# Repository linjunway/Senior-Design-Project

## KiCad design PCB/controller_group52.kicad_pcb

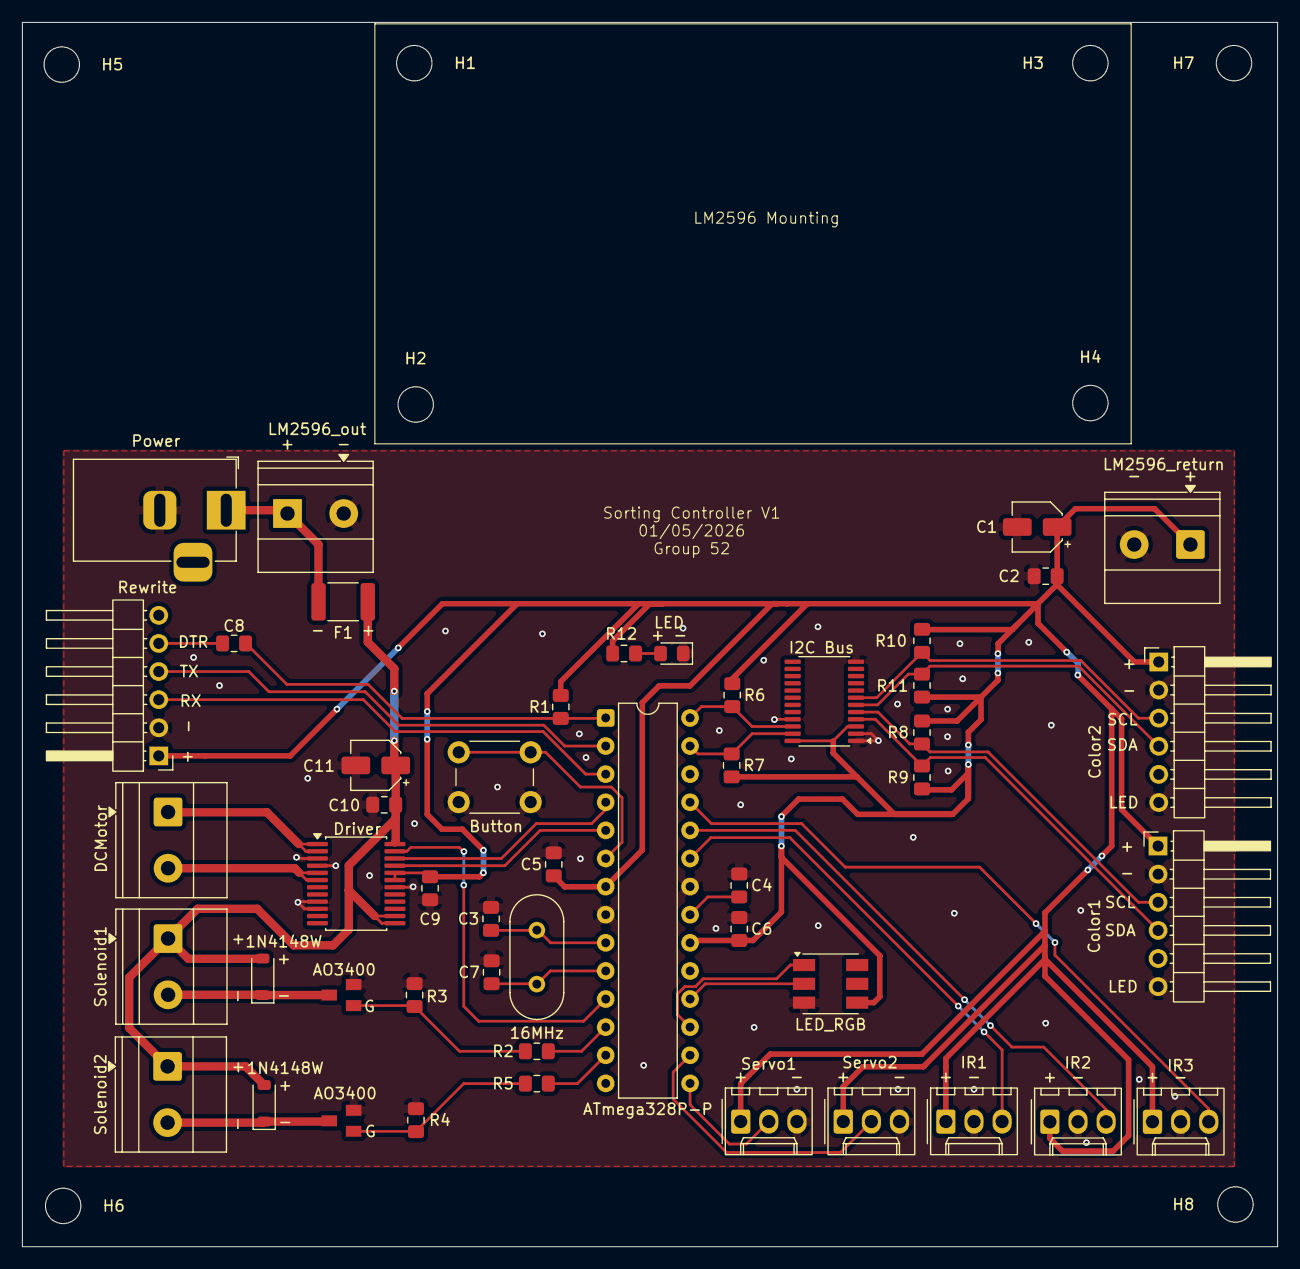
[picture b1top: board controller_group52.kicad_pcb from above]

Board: 2 copper layers, 113.4 x 110.6 mm, 57 parts (0 on the bottom side), 37 nets.

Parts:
C1, C11: 10uF; CP_Elec_4x5.4
C2: 1uF; C_0805_2012Metric_Pad1.18x1.45mm_HandSolder
C3, C7: 22pF; C_0805_2012Metric_Pad1.18x1.45mm_HandSolder
C4, C5, C6, C8, C9, C10: 0.1uF; C_0805_2012Metric_Pad1.18x1.45mm_HandSolder
D1, D2: 1N4148W; D_SOD-123
D3: LED_RGB; LED_RGB_5050-6
D4: LED; LED_0805_2012Metric_Pad1.15x1.40mm_HandSolder
F1: 2A12V; Fuse_1812_4532Metric_Pad1.30x3.40mm_HandSolder
H1, H2, H3, H4, H5, H6, H7, H8: MountingHole; MountingHole_3.2mm_M3
J1: IR1; Molex_KK-254_AE-6410-03A_1x03_P2.54mm_Vertical
J2: Power; BarrelJack_Horizontal
J3: Rewrite; PinHeader_1x06_P2.54mm_Horizontal
J4: Servo1; Molex_KK-254_AE-6410-03A_1x03_P2.54mm_Vertical
J5: Servo2; Molex_KK-254_AE-6410-03A_1x03_P2.54mm_Vertical
J6: DCMotor; TerminalBlock_Phoenix_MKDS-1,5-2-5.08_1x02_P5.08mm_Horizont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
J7: Solenoid1; TerminalBlock_Phoenix_MKDS-1,5-2-5.08_1x02_P5.08mm_Horizont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
J8: Solenoid2; TerminalBlock_Phoenix_MKDS-1,5-2-5.08_1x02_P5.08mm_Horizont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
J9: LM2596_out; TerminalBlock_Phoenix_MKDS-1,5-2-5.08_1x02_P5.08mm_Horizont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
J10: LM2596_return; TerminalBlock_Phoenix_MKDS-1,5-2-5.08_1x02_P5.08mm_Horizont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
J11: IR2; Molex_KK-254_AE-6410-03A_1x03_P2.54mm_Vertical
J12: IR3; Molex_KK-254_AE-6410-03A_1x03_P2.54mm_Vertical
R1: 10K; C_0805_2012Metric_Pad1.18x1.45mm_HandSolder
R2, R5, R12: 220; C_0805_2012Metric_Pad1.18x1.45mm_HandSolder
R3, R4, R6, R7, R8, R9, R10, R11: 10k; C_0805_2012Metric_Pad1.18x1.45mm_HandSolder
SW1: Button; SW_PUSH_6mm_H9.5mm
U1: ATmega328P-P; DIP-28_W7.62mm
U2: Driver; SSOP-24_5.3x8.2mm_P0.65mm
U3, U4: AO3400; SOT23
U5: I2C Bus; TSSOP-24_4.4x7.8mm_P0.65mm
U6: Color1; PinHeader_1x06_P2.54mm_Horizontal
U7: Color2; PinHeader_1x06_P2.54mm_Horizontal
Y1: 16MHz; Crystal_HC49-4H_Vertical

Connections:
+5V: C1.1, C2.2, C5.2, C6.1, C9.2, D3.4 (VCC), J1.1, J3.1, J4.1, J5.1, J10.1, J11.1, J12.1, R1.2, R6.2, R7.2, R8.2, R9.2, R10.2, R11.2, R12.2, U1.7 (VCC), U1.20 (AVCC), U2.19 (STBY), U2.20 (VCC), U5.3 (~RESET), U5.24 (VCC), U6.1 (VIN), U7.1 (VIN)
+12V: C10.2, C11.1, D1.2 (A), D2.2 (A), F1.2, J7.1, J8.1, U2.13 (VM2), U2.14 (VM3), U2.24 (VM1)
/A01: J6.1, U2.1 (AO1), U2.2 (AO1)
/A02: J6.2, U2.5 (AO2), U2.6 (AO2)
/AIN1: U1.5 (PD3), U2.21 (AIN1)
/AIN2: U1.4 (PD2), U2.22 (AIN2)
/Button: SW1.1, U1.6 (PD4)
/CI: D3.2 (CI), U1.18 (PB4)
/DI: D3.1 (DI), U1.17 (PB3)
/DTR: C8.2, R1.1, U1.1 (~RESET/PC6)
/PB1: J4.2, U1.15 (PB1)
/PB2: J5.2, U1.16 (PB2)
/PC0: J1.3, U1.23 (PC0)
/PC1: J11.3, U1.24 (PC1)
/PC2: J12.3, U1.25 (PC2)
/PD6: R2.2, R3.1, U4.1
/PD7: R4.1, R5.1, U3.1
/PWM: U1.11 (PD5), U2.23 (PWMA)
/RX: J3.3, U1.3 (PD1)
/SC0: R8.1, U5.5 (SC0), U6.3 (SCL)
/SC1: R10.1, U5.7 (SC1), U7.3 (SCL)
/SCL: R6.1, U1.28 (PC5), U5.22 (SCL)
/SD0: R9.1, U5.4 (SD0), U6.4 (SDA)
/SD1: R11.1, U5.6 (SD1), U7.4 (SDA)
/SDA: R7.1, U1.27 (PC4), U5.23 (SDA)
/TX: J3.4, U1.2 (PD0)
GND: C1.2, C2.1, C3.2, C4.2, C5.1, C6.2, C7.2, C9.1, C10.1, C11.2, D3.3 (GND), D4.1 (K), J1.2, J2.2, J3.2, J4.3, J5.3, J9.1, J10.2, J11.2, J12.2, R3.2, R4.2, SW1.2, U1.8 (GND), U1.22 (GND), U2.3 (PGND1), U2.4 (PGND1), U2.9 (PGND2), U2.10 (PGND2), U2.18 (GND), U3.2, U4.2, U5.1 (A0), U5.2 (A1), U5.12 (GND), U5.21 (A2), U6.2 (GND), U6.6 (LED), U7.2 (GND), U7.6 (LED)
unnamed: D1.1 (K), J8.2, U3.3
unnamed: D2.1 (K), J7.2, U4.3
unnamed: D4.2 (A), R12.1
unnamed: C8.1, J3.5
unnamed: F1.1, J2.1, J9.2
unnamed: C4.1, U1.21 (AREF)
unnamed: R2.1, U1.12 (PD6)
unnamed: R5.2, U1.13 (PD7)
unnamed: C3.1, U1.9 (XTAL1/PB6), Y1.2
unnamed: C7.1, U1.10 (XTAL2/PB7), Y1.1

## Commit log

2026-06-12 3D Models
2026-06-12 Code
2026-06-12 Project Details
